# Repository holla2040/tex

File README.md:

# tex
    RaspberryPi super controller board for multiple uses: for example museum static airplanes, solar tracker and off-grid water turbine automation.  

### features
<pre>
Overview
    Sensors
        8 analog inputs multiplexed to 12bit ADC at 3KSPS
            Used for temperature, light, voltage, current,
            pressure, flow, AC line sync, etc
        1 power supply current sense ADC

    User Interface
        2 board-mounted user input switches
        3 board-mounted indicator LEDS: R,G,B
        1 128x64 White OLED Display Module
        All connectors are plug-type for easy board replacement
        
    Control
        16 PWM-driven voltage outputs at 7A max with board indicator
        4 dry-contact 10A relays with COM/NC/NO connector
        2 120VAC/8A solid-state relays
        2 DC Motor H-bridge drivers with current sense
            * uses 4 of 16 outputs from above
            Motor direction indicator
        2 opto-coupled inputs for DC motor motion encoders
        2 stepper motor driver signalling outputs, EN/DIR/PULSE
        10 uncommitted digital +5 I/O signals
        
    Peripherals
        Board tempurature sensor
        Battery backed real-time clock 

    Power Supply
        12-26VDC operation, PWM outputs switch this voltage
        +5V DC/DC converter
        Reverse battery protection
        ATF automobile fuse
        
    Communication
        WiFi/Bluetooth 4.0/Ethernet supplied on Raspberry Pi 3
        RS-485 2/4 wire with termination resistor
        External I2C/Power/Ground connector
</pre>
<hr>
<pre>
Detailed
    DC motor 1 h-bridge            discrete fets
    DC motor 1 encoder             cpu interrupt opto-coupled
    DC motor 1 current detect      gain
    DC motor 2 h bridge            discrete fets
    DC motor 2 encoder             cpu interrupt opto-coupled
    DC motor 2 current detect      gain
    AC SSR 1                       i/o slow, unfused
    AC SSR 2                       i/o slow, unfused
    Temperature sensor 1           multiplexed, 10k pullup
    Temperature sensor 2           multiplexed, 10k pullup
    Temperature sensor 3           multiplexed, 10k pullup
    Temperature sensor 4           multiplexed, 10k pullup
    Pyranometer                    analog input with gain
    LED Driver 0                   pwm
    LED Driver 1                   pwm
    LED Driver 2                   pwm
    LED Driver 3                   pwm
    LED Driver 4                   pwm
    LED Driver 5                   pwm
    LED Driver 6                   pwm
    LED Driver 7                   pwm
    LED Driver 8                   pwm
    LED Driver 9                   pwm
    LED Driver 10                  pwm
    LED Driver 11                  pwm
    LED Driver 12                  pwm, push-pull coupled with 13
    LED Driver 13                  pwm, push-pull coupled with 12
    LED Driver 14                  pwm, push-pull coupled with 15
    LED Driver 15                  pwm, push-pull coupled with 14
    Relay 0                        i/o slow, NO/NC contacts
    Relay 1                        i/o slow, NO/NC contacts
    Relay 2                        i/o slow, NO/NC contacts
    Relay 3                        i/o slow, NO/NC contacts
    E-stop input                   cpu interrupt
    Water Pressure                 0-5VDC input
    Water Flow Rate                0-5VDC input with scaler
    External AC voltage detect     0-5VDC input with scaler, half-wave
    External AC current sensor     0-5VDC input with scaler, half-wave
    External AC frequency sensor   use adc from AC V or I sensor
    External 5VDC I/O 0            I/O slow, change interrupt exists
    External 5VDC I/O 1            I/O slow, change interrupt exists
    External 5VDC I/O 2            I/O slow, change interrupt exists
    External 5VDC I/O 3            I/O slow, change interrupt exists
    External 5VDC I/O 4            I/O slow, change interrupt exists
    External 5VDC I/O 5            I/O slow, change interrupt exists
    External 5VDC I/O 6            I/O slow, change interrupt exists
    External 5VDC I/O 7            I/O slow, change interrupt exists
    External 5VDC I/O 8            I/O slow, change interrupt exists
    External 5VDC I/O 9            I/O slow, change interrupt exists
    Stepper control A              enable, direction, step outputs
    Stepper control B              enable, direction, step outputs
    Power supply current monitor   high-side current monitor
    Display                        OLED 0.96 mount intended
    Reverse Battery Protection     FET biased forward bias protection 
</pre>

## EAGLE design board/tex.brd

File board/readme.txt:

This information, board files, assembly instructions and bill of
materials are company confidental.
Not for distribution.

board
    tex

version
    v0.1

date
    160906

svn revision
    n/a

fudicials at
    6mm,6mm
    194mm,94mm

2 layer description
    2 layer board
        crc component cream
        plc component side silkscreen
        stc component side solder stop mask
        cmp component side copper
        sol solder side copper
        sts solder side solder stop mask
        pls solder side silkscreen
        crs solder cream

        drd drill data
        dri drill info
        gpi gerber info

2 layer stack up sequence
    top     x.cmp
    bottom  x.sol

contact info
    Craig Hollabaugh
    970 690 4911
    craig@hollabaugh.com

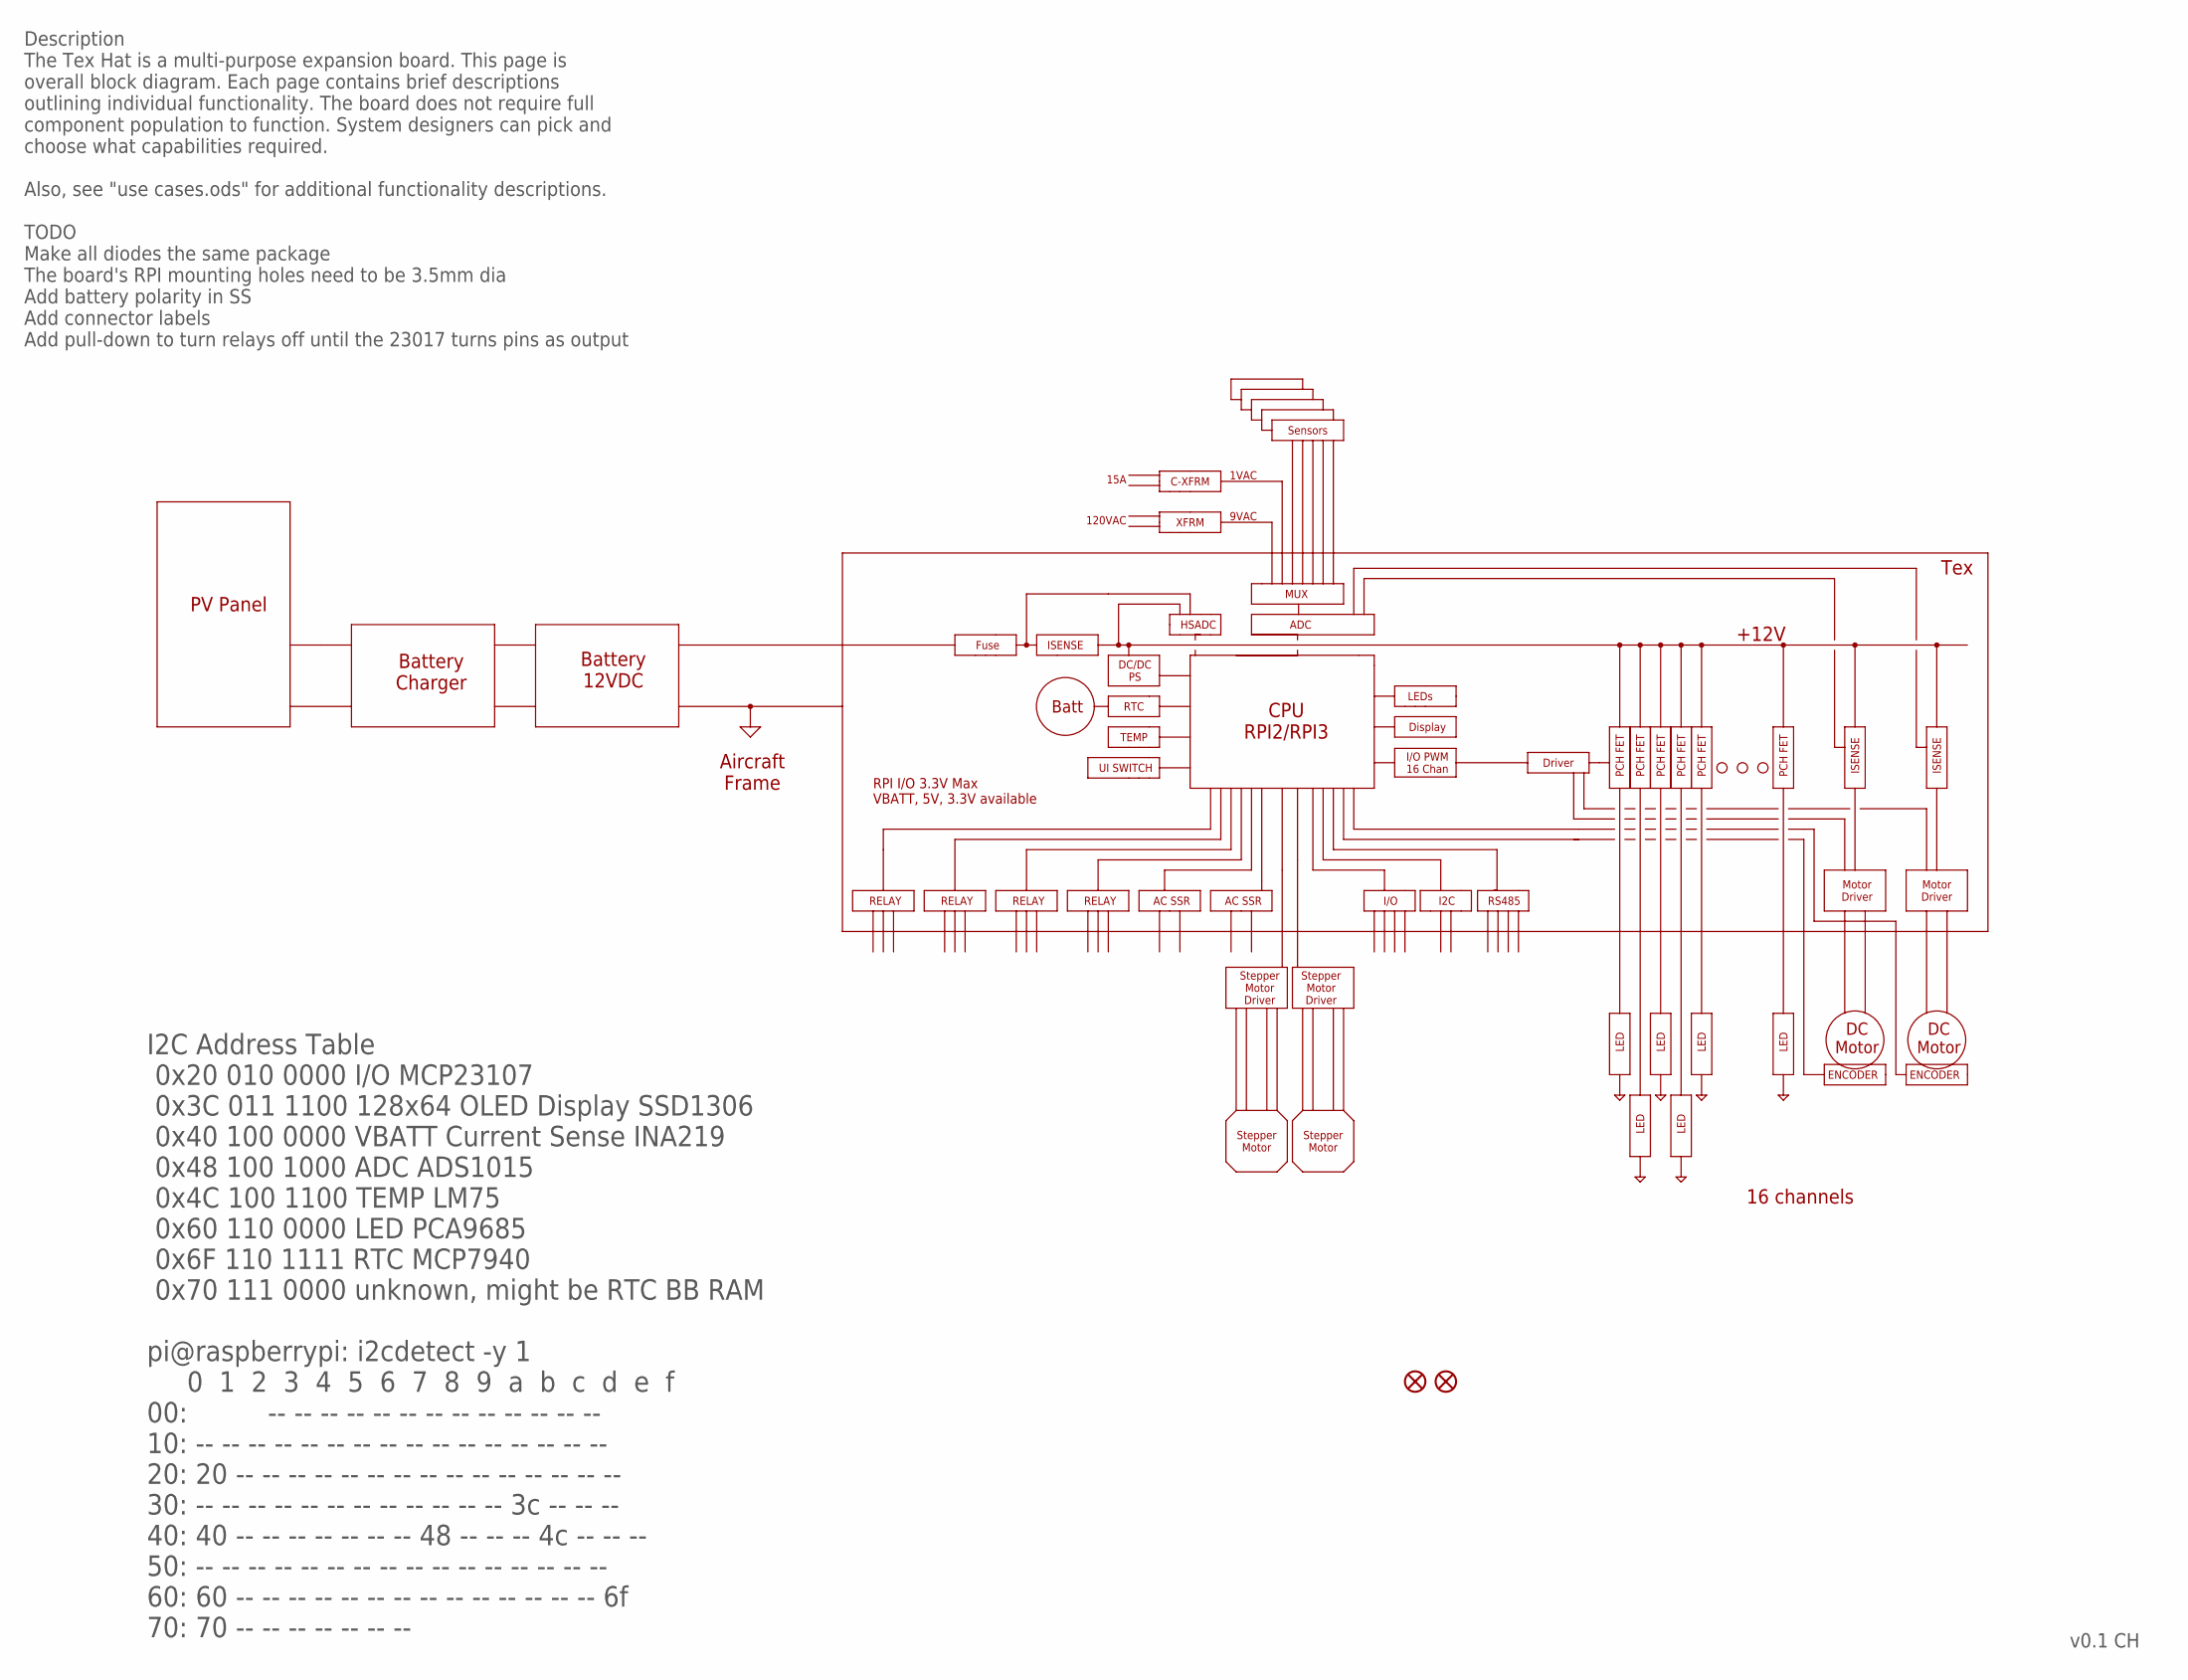
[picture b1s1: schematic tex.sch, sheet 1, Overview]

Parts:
JP1, JP3: FIDUCIALUFIDUCIAL; MICRO-FIDUCIAL

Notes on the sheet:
PV Panel
Battery Charger
Battery 12VDC
Aircraft Frame
Tex
DC/DC PS
CPU RPI2/RPI3
Display
+12V
I/O PWM 16 Chan
PCH FET
Driver
LED
RELAY
Motor Driver
Stepper Motor Driver
DC Motor
Stepper Motor
16 channels
TEMP
ADC
Fuse
AC SSR
I/O
LEDs
RPI I/O 3.3V Max VBATT, 5V, 3.3V available
I2C
HSADC
RS485
RTC
Sensors
MUX
ISENSE
Description The Tex Hat is a multi-purpose expansion board. This page is overall block diagram. Each page contains brief descriptions outlining individual functionality. The board does not require full component population to function. System designers can pick and choose what capabilities required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
I2C Address Table 0x20 010 0000 I/O MCP23107 0x3C 011 1100 128x64 OLED Display SSD1306 0x40 100 0000 VBATT Current Sense INA219 0x48 100 1000 ADC ADS1015 0x4C 100 1100 TEMP LM75 0x60 110 0000 LED PCA9685 0x6F 110 1111 RTC MCP7940 0x70 111 0000 unknown, might be RTC BB RAM pi@raspberrypi: i2cdetect 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
Batt
UI SWITCH
XFRM
120VAC
9VAC

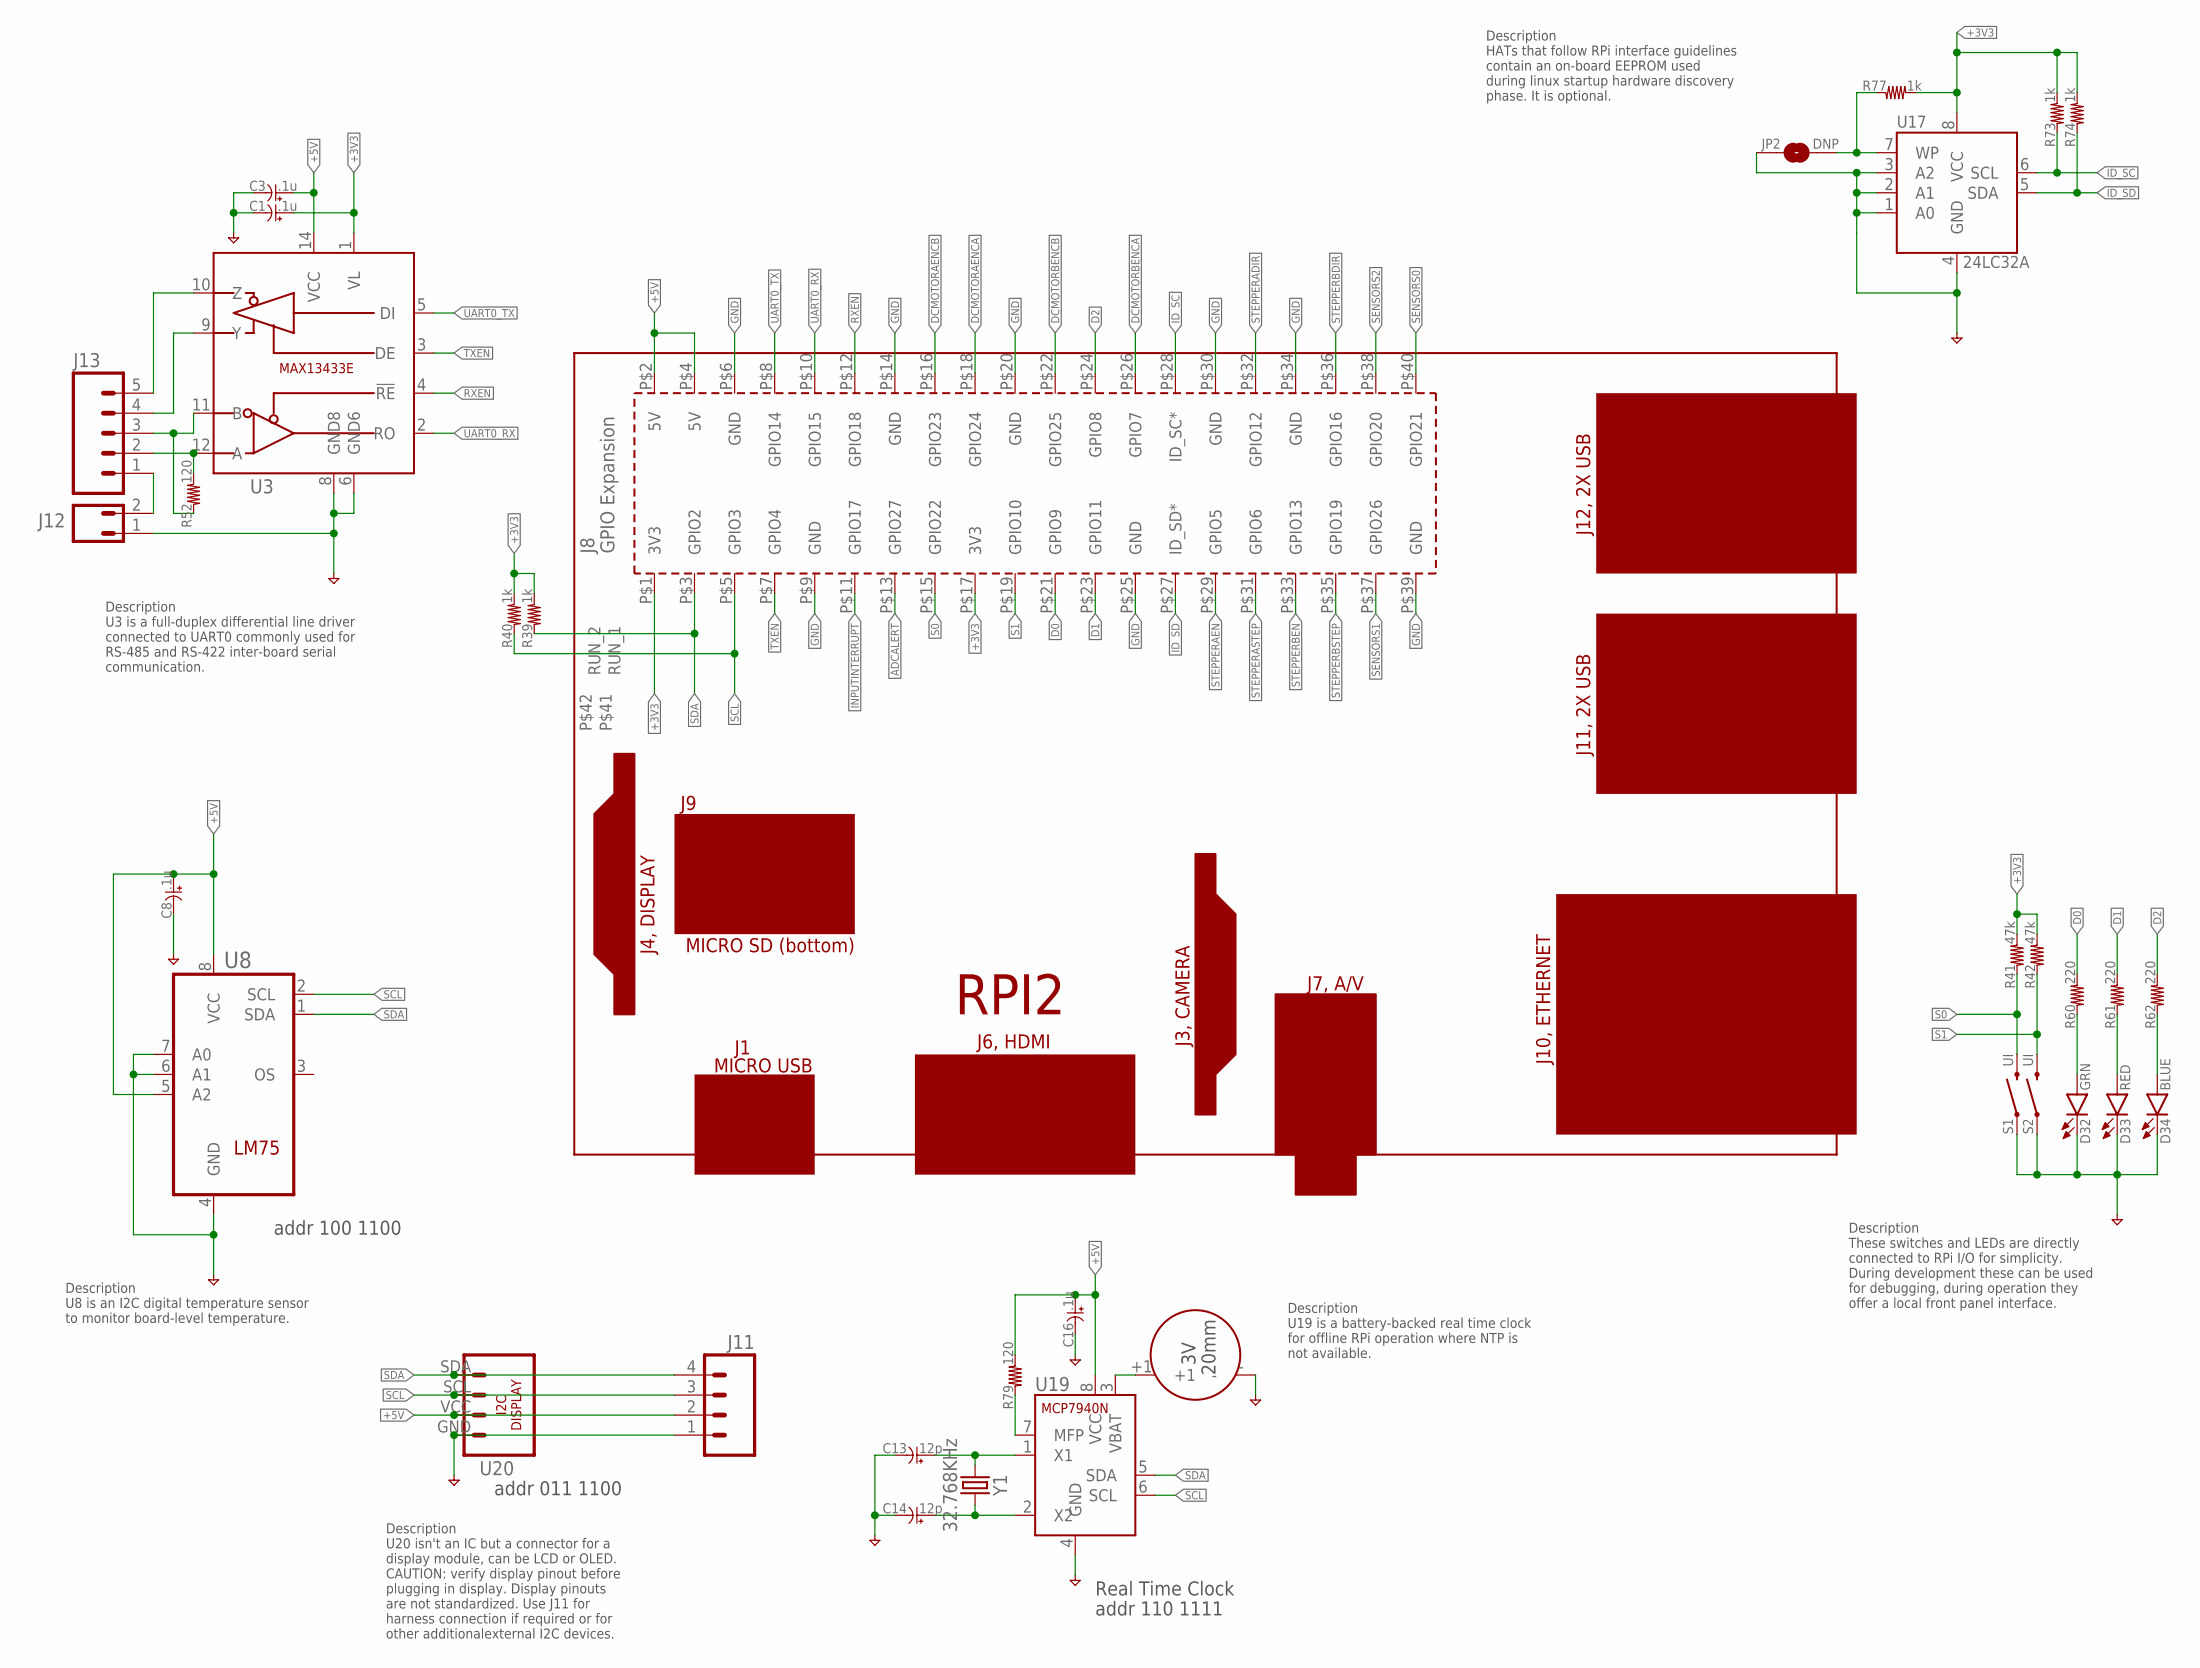
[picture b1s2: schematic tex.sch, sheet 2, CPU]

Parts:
B1: CR2032; BAT-HLD-001
C1, C3, C8, C16: .1u; C0603
C13, C14: 12p; C0603
D32: GRN; LED0603
D33: RED; LED0603
D34: BLUE; LED0603
J11: CONN-04-0.1; 1X04
J12: CONN-02-0.1; 1X02
J13: CONN-05-PLUGIN-SCREW; CONN-3.81MM-KF2EDG-5
JP2: DNP; PAD-JUMPER-2-NO_NO_SILK
PCB1: BOARD-RPI2
R39, R40, R73, R74, R77: 1k; R0603
R41, R42: 47k; R0603
R52, R79: 120; R0603
R60, R61, R62: 220; R0603
S1, S2: UI; TACTILE-SWITCH-6MMX3.5MM
U3: MAX13433E; SO14
U8: LM75; SO08
U17: 24LC32A; SO08
U19: MCP7940N; SO08
U20: DISP-I2C-4PIN; DISP-I2C-4PIN-0.96
Y1: 32.768KHz; ABS25

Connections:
+3V3: C1.1, PCB1.P$1 (3V3), PCB1.P$17 (3V3), R39.2, R40.2, R41.2, R42.2, R73.2, R74.2, R77.2, U3.1 (VL), U17.8 (VCC)
+5V: C3.1, C8.1, C16.1, J11.2, PCB1.P$2 (5V), PCB1.P$4 (5V), R79.2, U3.14 (VCC), U8.5 (A2), U8.8 (VCC), U19.8 (VCC), U20.VCC; also elsewhere on the board
ADCALERT: PCB1.P$13 (GPIO27); also elsewhere on the board
D0: PCB1.P$21 (GPIO9), R60.2
D1: PCB1.P$23 (GPIO11), R61.2
D2: PCB1.P$24 (GPIO8), R62.2
DCMOTORAENCA: PCB1.P$18 (GPIO24); also elsewhere on the board
DCMOTORAENCB: PCB1.P$16 (GPIO23); also elsewhere on the board
DCMOTORBENCA: PCB1.P$26 (GPIO7); also elsewhere on the board
DCMOTORBENCB: PCB1.P$22 (GPIO25); also elsewhere on the board
GND: B1.-, C1.2, C3.2, C8.2, C13.2, C14.2, C16.2, D32.C, D33.C, D34.C, J11.1, J12.1, JP2.1, PCB1.P$6 (GND), PCB1.P$9 (GND), PCB1.P$14 (GND), PCB1.P$20 (GND), PCB1.P$25 (GND), PCB1.P$30 (GND), PCB1.P$34 (GND), PCB1.P$39 (GND), S1.P$1 (1), S2.P$1 (1), U3.6 (GND6), U3.8 (GND8), U8.4 (GND), U8.6 (A1), U8.7 (A0), U17.1 (A0), U17.2 (A1), U17.3 (A2), U17.4 (GND), U19.4 (GND), U20.GND; also elsewhere on the board
ID_SC: PCB1.P$28 (ID_SC*), R73.1, U17.6 (SCL)
ID_SD: PCB1.P$27 (ID_SD*), R74.1, U17.5 (SDA)
INPUTINTERRUPT: PCB1.P$11 (GPIO17); also elsewhere on the board
unnamed: C13.1, U19.1 (X1), Y1.1
unnamed: C14.1, U19.2 (X2), Y1.4 (2)
unnamed: J13.2, R52.2, U3.12 (A)
unnamed: J13.3, R52.1, U3.11 (B)
unnamed: J13.4, U3.9 (Y)
unnamed: J13.5, U3.10 (Z)
unnamed: J12.2, J13.1
unnamed: D32.A, R60.1
unnamed: D33.A, R61.1
unnamed: D34.A, R62.1
unnamed: JP2.2, R77.1, U17.7 (WP)
unnamed: B1.+1, U19.3 (VBAT)
unnamed: R79.1, U19.7 (MFP)
RXEN: PCB1.P$12 (GPIO18), U3.4 (!RE)
S0: PCB1.P$15 (GPIO22), R41.1, S1.P$2 (2)
S1: PCB1.P$19 (GPIO10), R42.1, S2.P$2 (2)
SCL: J11.3, PCB1.P$5 (GPIO3), R40.1, U8.2 (SCL), U19.6 (SCL), U20.SCL; also elsewhere on the board
SDA: J11.4, PCB1.P$3 (GPIO2), R39.1, U8.1 (SDA), U19.5 (SDA), U20.SDA; also elsewhere on the board
SENSORS0: PCB1.P$40 (GPIO21); also elsewhere on the board
SENSORS1: PCB1.P$37 (GPIO26); also elsewhere on the board
SENSORS2: PCB1.P$38 (GPIO20); also elsewhere on the board
STEPPERADIR: PCB1.P$32 (GPIO12); also elsewhere on the board
STEPPERAEN: PCB1.P$29 (GPIO5); also elsewhere on the board
STEPPERASTEP: PCB1.P$31 (GPIO6); also elsewhere on the board
STEPPERBDIR: PCB1.P$36 (GPIO16); also elsewhere on the board
STEPPERBEN: PCB1.P$33 (GPIO13); also elsewhere on the board
STEPPERBSTEP: PCB1.P$35 (GPIO19); also elsewhere on the board
TXEN: PCB1.P$7 (GPIO4), U3.3 (DE)
UART0_RX: PCB1.P$10 (GPIO15), U3.2 (RO)
UART0_TX: PCB1.P$8 (GPIO14), U3.5 (DI)

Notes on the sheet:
Real Time Clock
addr 100 1100
addr 110 1111
addr 011 1100
Description U3 is a full-duplex differential line driver connected to UART0 commonly used for RS-485 and RS-422 inter-board serial communication.
Description U8 is an I2C digital temperature sensor to monitor board-level temperature.
Description U20 isn't an IC but a connector for a display module, can be LCD or OLED. CAUTION: verify display pinout before plugging in display. Display pinouts are not standardized. Use J11 for harness connection if required or for other additionalexternal I2C devices.
Description U19 is a battery-backed real time clock for offline RPi operation where NTP is not available.
Description These switches and LEDs are directly connected to RPi I/O for simplicity. During development these can be used for debugging, during operation they offer a local front panel interface.
Description HATs that follow RPi interface guidelines contain an on-board EEPROM used during linux startup hardware discovery phase. It is optional.

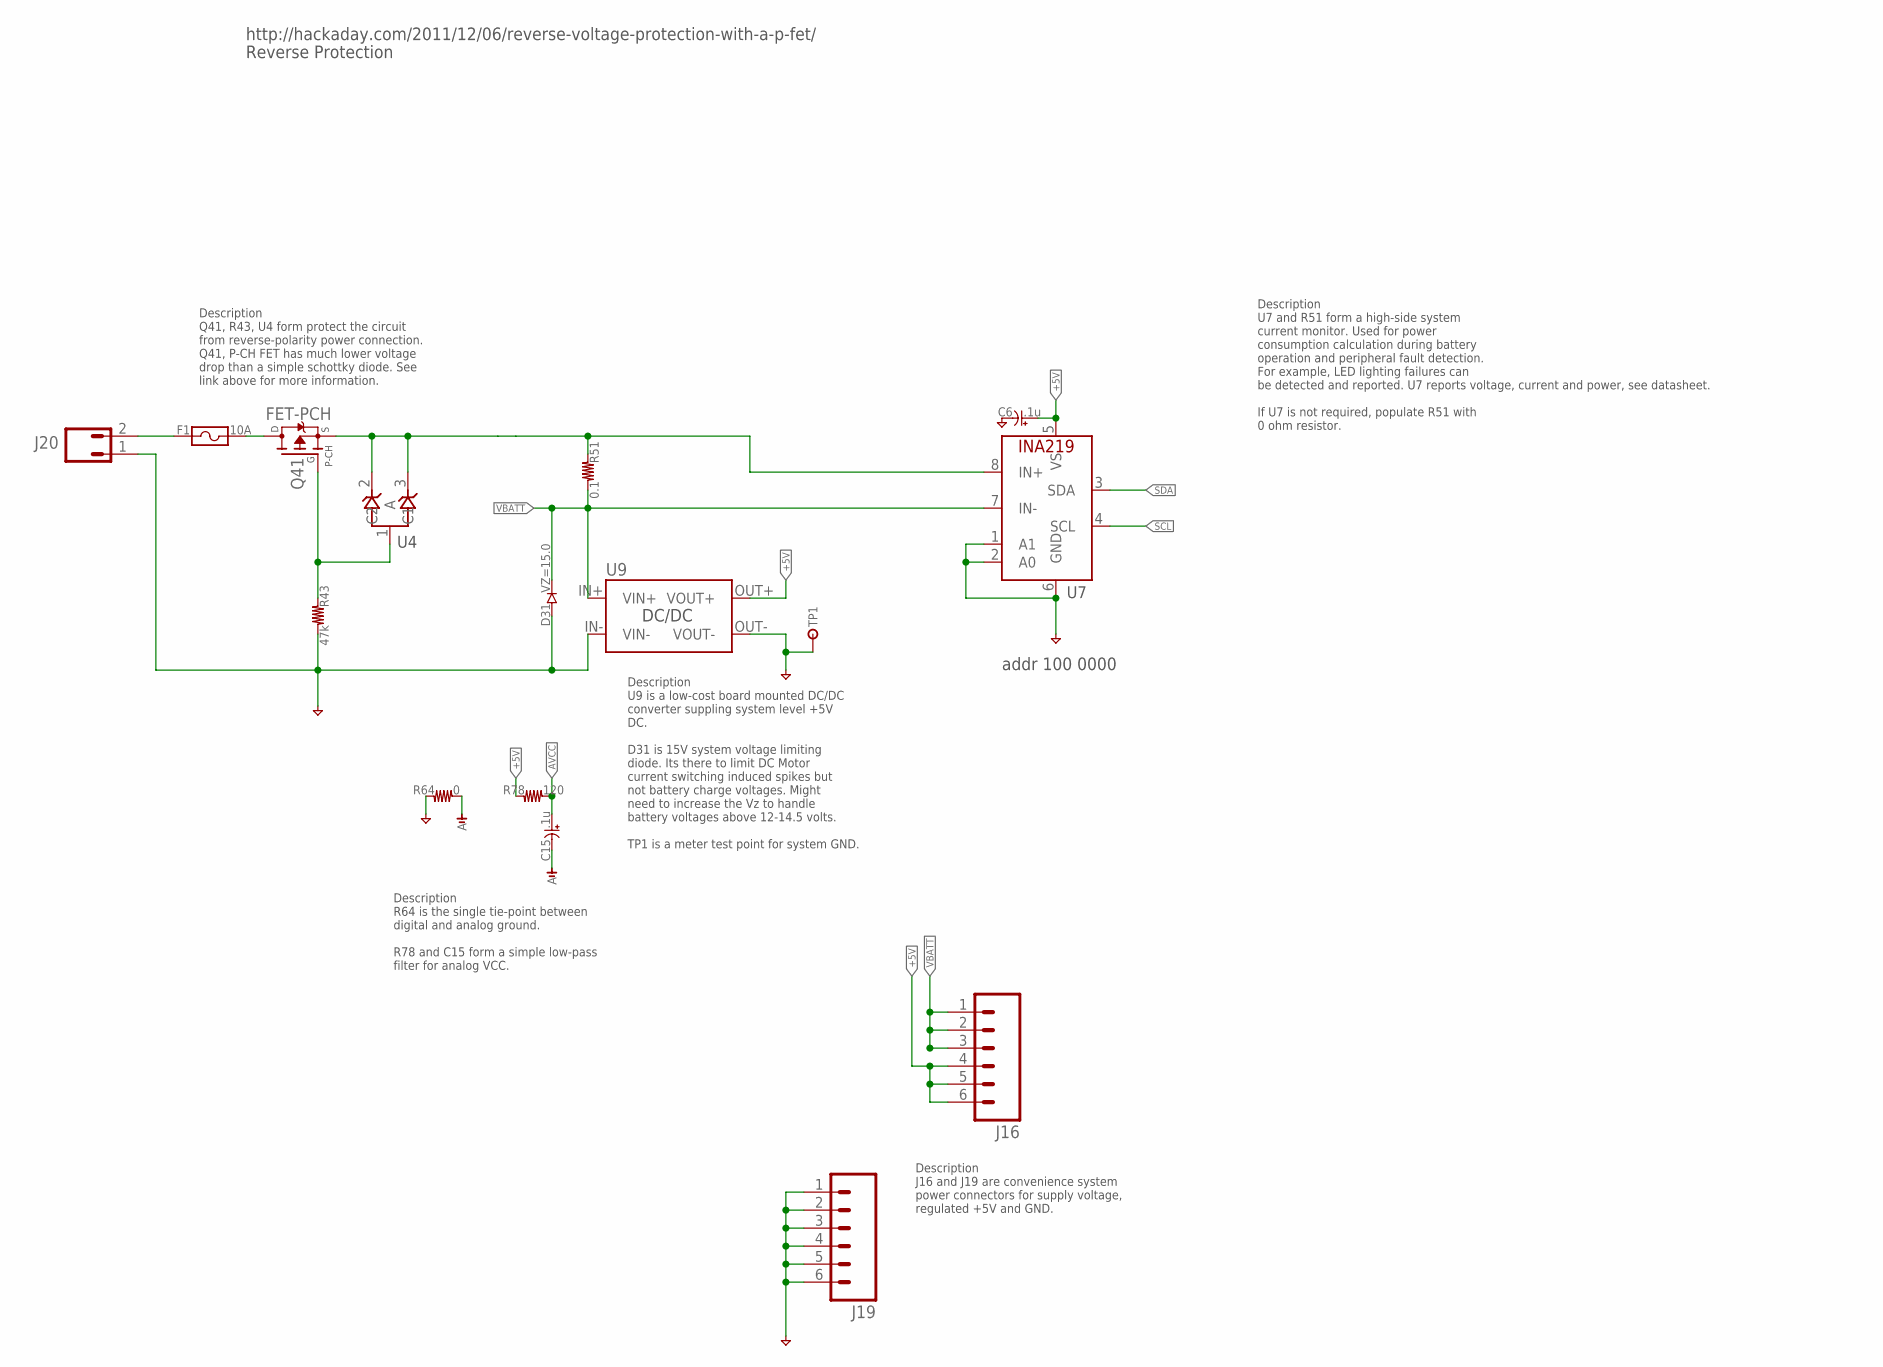
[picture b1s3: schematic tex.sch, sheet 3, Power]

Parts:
C6, C15: .1u; C0603
D31: VZ=15.0; DO-214AC(SMA)
F1: 10A; 3557-2
J16, J19: CONN-06-PLUGIN-SCREW; CONN-3.81MM-KF2EDG-6
J20: CONN-02-6.35MM; CONN-OSTT702
Q41: FET-PCH; TO252
R43: 47k; R0603
R51: 0.1; R1210
R64: 0; R0603
R78: 120; R0603
TP1: TESTPOINTTHRU; TPTHRU
U4: AZ23C5V1; SOT-23
U7: INA219; SOIC8
U9: DCDC-CONVERTER-LM2577-BOARD; DCDC-LM2577-BOARD

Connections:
+5V: C6.1, J16.4, J16.5, J16.6, R78.1, U7.5 (VS), U9.OUT+ (VOUT+); also elsewhere on the board
AGND: C15.2, R64.2; also elsewhere on the board
AVCC: C15.1, R78.2; also elsewhere on the board
GND: C6.2, D31.A, J19.1, J19.2, J19.3, J19.4, J19.5, J19.6, J20.1, R43.2, R64.1, TP1.1, U7.1 (A1), U7.2 (A0), U7.6 (GND), U9.IN- (VIN-), U9.OUT- (VOUT-); also elsewhere on the board
unnamed: Q41.1 (G), R43.1, U4.1 (A)
unnamed: F1.1@1, F1.1@2, J20.2
unnamed: F1.2@1, F1.2@2, Q41.3 (D)
SCL: U7.4 (SCL); also elsewhere on the board
SDA: U7.3 (SDA); also elsewhere on the board
VBATT: D31.C, J16.1, J16.2, J16.3, R51.2, U7.7 (IN-), U9.IN+ (VIN+); also elsewhere on the board
VBATTISENSE: Q41.2 (S), R51.1, U4.2 (C2), U4.3 (C1), U7.8 (IN+)

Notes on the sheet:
Reverse Protection
http://hackaday.com/2011/12/06/reverse-voltage-protection-with-a-p-fet/
addr 100 0000
Description Q41, R43, U4 form protect the circuit from reverse-polarity power connection. Q41, P-CH FET has much lower voltage drop than a simple schottky diode. See link above for more information.
Description U7 and R51 form a high-side system current monitor. Used for power consumption calculation during battery operation and peripheral fault detection. For example, LED lighting failures can be detected and reported. U7 reports voltage, current and power, see datasheet. If U7 is not require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
Description U9 is a low-cost board mounted DC/DC converter suppling system level +5V DC. D31 is 15V system voltage limiting diode. Its there to limit DC Motor current switching induced spikes but not battery charge voltages. Might need to increase the Vz to handle battery voltages above 12-14.5 vol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
Description R64 is the single tie-point between digital and analog ground. R78 and C15 form a simple low-pass filter for analog VCC.
Description J16 and J19 are convenience system power connectors for supply voltage, regulated +5V and GND.

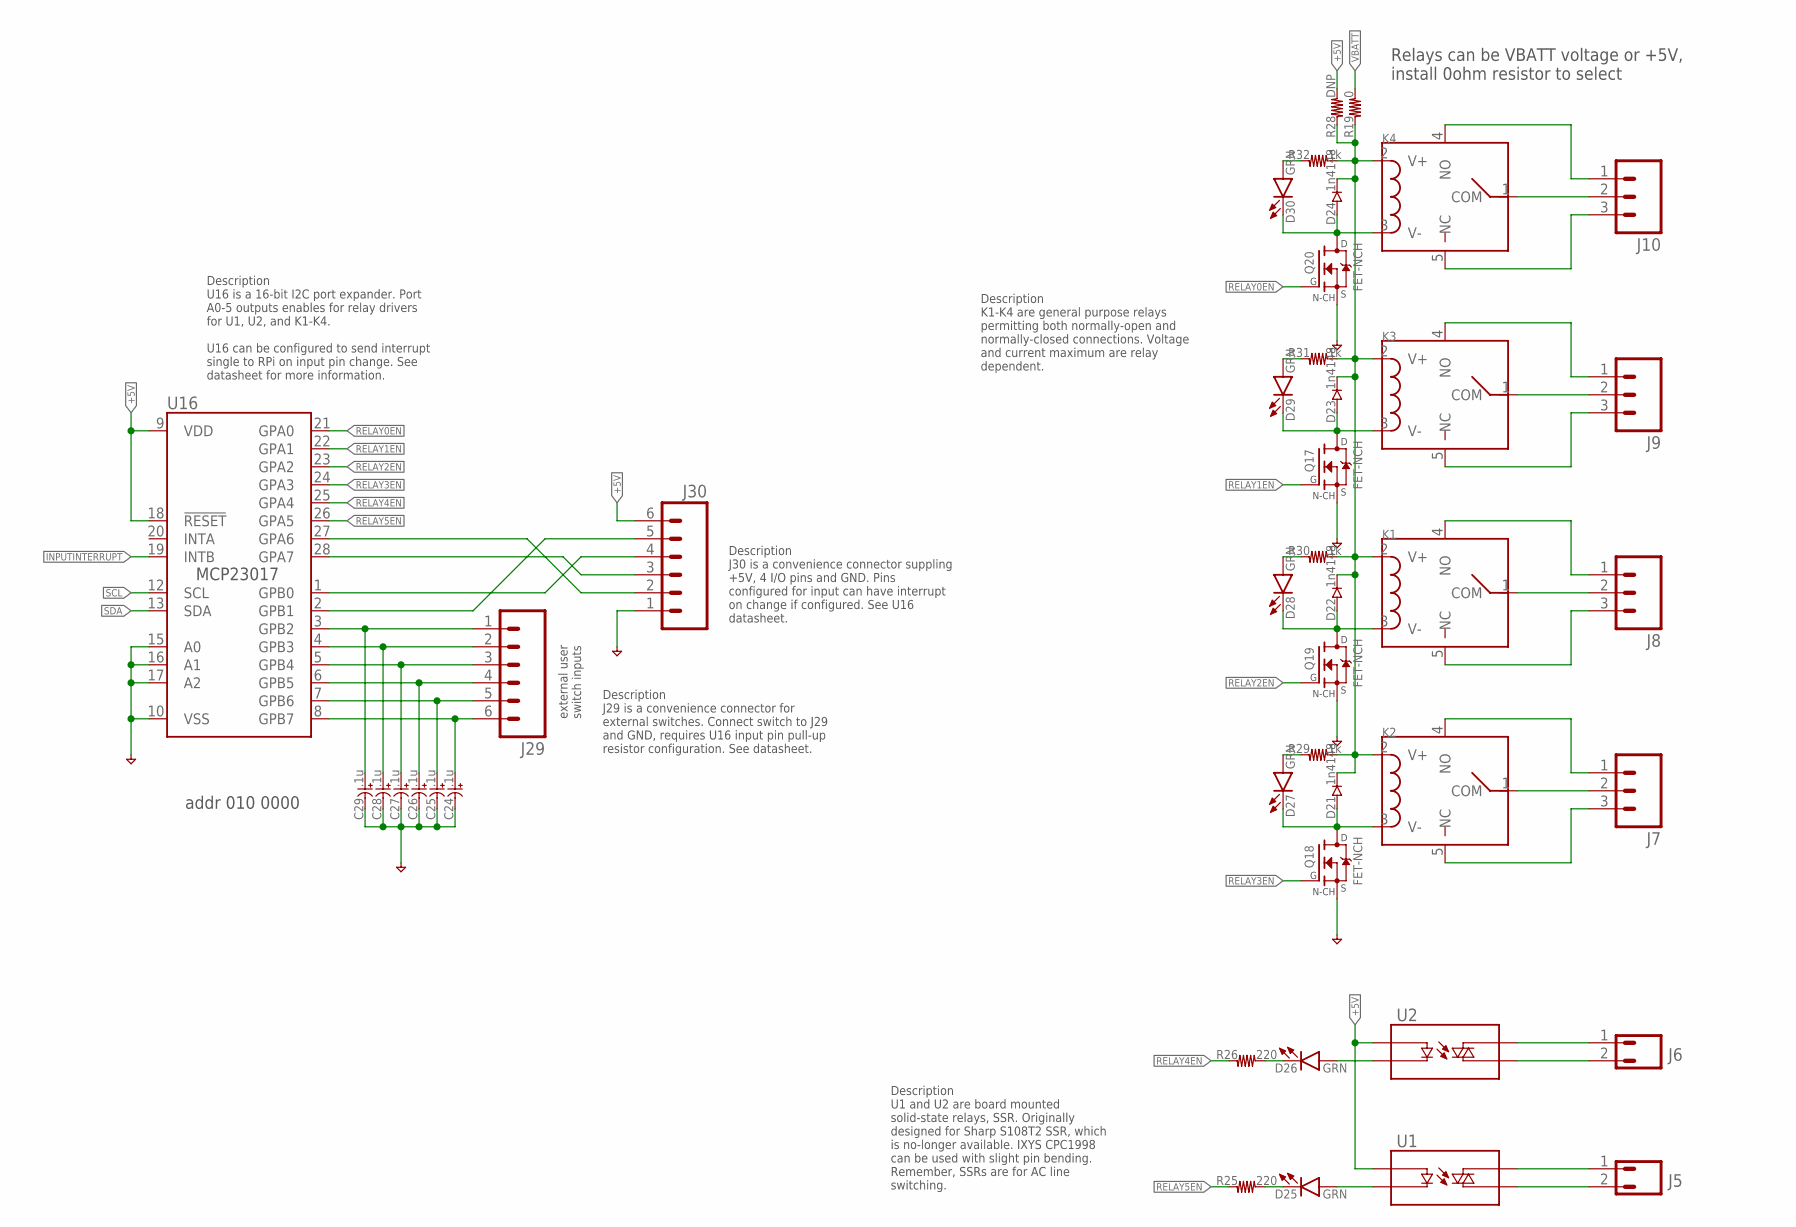
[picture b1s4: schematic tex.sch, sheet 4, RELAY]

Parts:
C24, C25, C26, C27, C28, C29: .1u; C0603
D21, D22, D23, D24: 1n4148; SOD-523
D25, D26, D27, D28, D29, D30: GRN; LED0603
J5, J6: CONN-02-PLUGIN-SCREW; CONN-3.81MM-KF2EDG-2
J7, J8, J9, J10: CONN-03-PLUGIN-SCREW; CONN-3.81MM-KF2EDG-3
J29, J30: CONN-06-PLUGIN-SCREW; CONN-3.81MM-KF2EDG-6
K1, K2, K3, K4: RELAY-SPST-19X15X15MM; RELAY-SPST-19.0X15.0X15.0MM
Q17, Q18, Q19, Q20: FET-NCH; SOT23-3
R19: 0; R0603
R25, R26: 220; R0603
R28: DNP; R0603
R29, R30, R31, R32: 1k; R0603
U1, U2: RELAY-S108T02PTH; RELAY-S108T02
U16: MCP23017; SO28W

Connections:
+5V: J30.6, R28.2, U1.3 (+), U2.3 (+), U16.9 (VDD), U16.18 (!RESET); also elsewhere on the board
GND: C24.2, C25.2, C26.2, C27.2, C28.2, C29.2, J30.1, Q17.2 (S), Q18.2 (S), Q19.2 (S), Q20.2 (S), U16.10 (VSS), U16.15 (A0), U16.16 (A1), U16.17 (A2); also elsewhere on the board
GND4: D21.A, D27.C, K2.3 (V-), Q18.3 (D)
INPUTINTERRUPT: U16.19 (INTB); also elsewhere on the board
unnamed: J30.2, U16.27 (GPA6)
unnamed: J30.5, U16.2 (GPB1)
unnamed: J30.4, U16.1 (GPB0)
unnamed: J30.3, U16.28 (GPA7)
unnamed: J6.1, U2.1 (T1)
unnamed: C29.1, J29.1, U16.3 (GPB2)
unnamed: C28.1, J29.2, U16.4 (GPB3)
unnamed: C27.1, J29.3, U16.5 (GPB4)
unnamed: C26.1, J29.4, U16.6 (GPB5)
unnamed: C25.1, J29.5, U16.7 (GPB6)
unnamed: C24.1, J29.6, U16.8 (GPB7)
unnamed: J10.2, K4.1 (COM)
unnamed: J10.1, K4.4 (NO)
unnamed: J10.3, K4.5 (NC)
unnamed: D29.A, R31.1
unnamed: D22.A, D28.C, K1.3 (V-), Q19.3 (D)
unnamed: D23.A, D29.C, K3.3 (V-), Q17.3 (D)
unnamed: J9.2, K3.1 (COM)
unnamed: J9.1, K3.4 (NO)
unnamed: J9.3, K3.5 (NC)
unnamed: J8.2, K1.1 (COM)
unnamed: J8.1, K1.4 (NO)
unnamed: J8.3, K1.5 (NC)
unnamed: J7.1, K2.4 (NO)
unnamed: J7.2, K2.1 (COM)
unnamed: J7.3, K2.5 (NC)
unnamed: D21.C, D22.C, D23.C, D24.C, K1.2 (V+), K2.2 (V+), K3.2 (V+), K4.2 (V+), R19.1, R28.1, R29.2, R30.2, R31.2, R32.2
unnamed: D30.A, R32.1
unnamed: D28.A, R30.1
unnamed: D27.A, R29.1
unnamed: D24.A, D30.C, K4.3 (V-), Q20.3 (D)
unnamed: J6.2, U2.2 (T2)
unnamed: J5.1, U1.1 (T1)
unnamed: J5.2, U1.2 (T2)
unnamed: D26.C, R26.2
unnamed: D25.C, R25.2
unnamed: D26.A, U2.4 (-)
unnamed: D25.A, U1.4 (-)
RELAY0EN: Q20.1 (G), U16.21 (GPA0)
RELAY1EN: Q17.1 (G), U16.22 (GPA1)
RELAY2EN: Q19.1 (G), U16.23 (GPA2)
RELAY3EN: Q18.1 (G), U16.24 (GPA3)
RELAY4EN: R26.1, U16.25 (GPA4)
RELAY5EN: R25.1, U16.26 (GPA5)
SCL: U16.12 (SCL); also elsewhere on the board
SDA: U16.13 (SDA); also elsewhere on the board
VBATT: R19.2; also elsewhere on the board

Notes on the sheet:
addr 010 0000
external user switch inputs
Relays can be VBATT voltage or +5V, install 0ohm resistor to select
Description U16 is a 16-bit I2C port expander. Port A0-5 outputs enables for relay drivers for U1, U2, and K1-K4. U16 can be configured to send interrupt single to RPi on input pin change. See datasheet for more information.
Description K1-K4 are general purpose relays permitting both normally-open and normally-closed connections. Voltage and current maximum are relay dependent.
Description J30 is a convenience connector suppling +5V, 4 I/O pins and GND. Pins configured for input can have interrupt on change if configured. See U16 datasheet.
Description J29 is a convenience connector for external switches. Connect switch to J29 and GND, requires U16 input pin pull-up resistor configuration. See datasheet.
Description U1 and U2 are board mounted solid-state relays, SSR. Originally designed for Sharp S108T2 SSR, which is no-longer available. IXYS CPC1998 can be used with slight pin bending. Remember, SSRs are for AC line switching.
